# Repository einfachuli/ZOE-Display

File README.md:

# ZOE-Display

<pre>
!!!!!!!!!!!!!!!!!!!!!!!!!!!!!!!!!!!!!!!!!!!!!!!!!!!!!!!!!!!!!!!!!!
!!!! OHNE GEWÄHR, ALLES AUF EIGENE GEFAHR, NUR ZU TESTZWECKEN !!!!
!!!!!!!!!!!!!!!!!!!!!!!!!!!!!!!!!!!!!!!!!!!!!!!!!!!!!!!!!!!!!!!!!!
</pre>

## Verwendete Bauteile

- ESP32-Development-Board (z.B. https://www.ebay.de/itm/162572643462 oder https://www.amazon.de/gp/product/B071P98VTG)
- 2,8 Zoll 240 x 320 SPI TFT Panel resistiver Touchscreen (mit Display-Treiber ILI9341, z.B. https://www.amazon.de/gp/product/B0749N3S33/)
- alternativ mit kapazitivem Touchscreen (Adafruit 1947 mit Display-Treiber ILI9341, z.B. https://www.amazon.de/gp/product/B00R3R65C0/ oder https://www.mouser.de/ProductDetail/Adafruit/1947?qs=GURawfaeGuArmJSJoJoDJA%3D%3D)
- SD-Karte (bei resistivem Touchscreen) bzw. microSD-Karte (bei kapazitivem Touchscreen)
- optional GPS-Modul (z.B. https://www.ebay.de/itm/163636495985 oder https://www.amazon.de/gp/product/B01N38EMBF/)
- Kleinteile (siehe Ordner zur jeweiligen Platinen-Version)

## Verbindungen mit resistivem Touchscreen
<pre>
ESP32 Dev Board Pinout

Wohin           Bezeich.       ESP32 Pins       Bezeich.    Wohin

                            3V3         GND
                            EN          G23     MOSI        Display,Touch,SD
                ST          G36         G22
                            G39         G1      (TX)
                            G34         G3      (RX)
                (CAN2 RX)   G35         G21     CS          Touch
                (CAN2 TX)   G32         GND
                HR          G33         G19     MISO        Display,Touch,SD
                            G25         G18     SCLK        Display,Touch,SD
GPS             GPS TX      G26         G5 
GPS             GPS RX      G27         G17     CAN TX      CAN Bus
BUZZER+                     G14         G16     CAN RX      CAN Bus 
                POWER OFF   G12         G4      RST         Display
                            GND         G0      (BOOT)
SD              CS          G13         G2      DC          Display
                (Flash)     G9          G15     CS          Display
                (Flash)     G10         G8      (Flash)
                (Flash)     G11         G7      (Flash)
                            5V          G6      (Flash)
</pre>                    
RX und TX gibt den Pin an, mit dem es verbunden werden muss. GPS TX muss also auf den Pin
TX am GPS Modul! 

CAN2 ist derzeit experimentell. 

ST = Screen Turn, ST=1 (mit 10k auf 3V3) -> Bildschirm um 180 Grad gedreht

HR = Helligkeitsregelung, kann einen Transistor ansteuern, über den die LED-Hintergrundbeleuchtung des Displays gedimmt werden kann.

POWER OFF = Ausschalt-Pin für die Stromversorgung über den OBD-Port

## Verbindungen mit kapazitivem Touchscreen
<pre>
ESP32 Dev Board Pinout

Wohin           Bezeich.       ESP32 Pins       Bezeich.    Wohin

                            3V3         GND
                            EN          G23     SPI MOSI    Display
                ST          G36         G22     I²C SCL     Display
                            G39         G1      (TX)
                            G34         G3      (RX)
                (CAN2 RX)   G35         G21 
                (CAN2 TX)   G32         GND
Display         HR          G33         G19     SPI MISO    Display
Display         I²C SDA     G25         G18     SPI SCLK    Display
GPS             GPS TX      G26         G5
GPS             GPS RX      G27         G17     CAN TX      CAN Bus
BUZZER+                     G14         G16     CAN RX      CAN Bus 
                POWER OFF   G12         G4      RST         Display
                            GND         G0      (BOOT)
Display         CARDCS      G13         G2      DC          Display
                (Flash)     G9          G15     CS          Display
                (Flash)     G10         G8      (Flash)
                (Flash)     G11         G7      (Flash)
                            5V          G6      (Flash)
</pre>                    
RX und TX gibt den Pin an, mit dem es verbunden werden muss. GPS TX muss also auf den Pin
TX am GPS Modul! 

CAN2 ist derzeit experimentell. 

ST = Screen Turn, ST=1 (mit 10k auf 3V3) -> Bildschirm um 180 Grad gedreht

HR = Helligkeitsregelung, an Pin GPIO33 liegt ein PWM Signal an, welches über Pin D5 am Display
(neben CARDCS) die Regelung der Displayhelligkeit erlaubt. Achtung: Die Lötbrücke #5 auf der 
Displayplatine muss hierfür gesetzt werden.

POWER OFF = Ausschalt-Pin für die Stromversorgung über den OBD-Port
                    
## Allgemein
-  Beim Betrieb des resistiven Displays mit 3,3 V sollte der Jumper J1 am Display gesetzt (verbunden) werden (Ausschalten
des Spannungsreglers des Displays, sonst sinken die 3,3 V auf irgendwas unter 3 V). Der Touch IRQ Pin bleibt leer.
- Das Display mit kapazitivem Touchscreen erhält 5 V Versorgungsspannung. Falls das verwendete Display keine IOREF-Lötbrücke besitzt bzw. diese auf 5 V gesetzt wurde, muss eine geeignete Maßnahme vorgesehen werden, um die Spannungspegel am I²C-Bus auf max. 3,3 V zu begrenzen (das Display zieht die Leitungen nämlich mit 10-kΩ-Pull-Up-Widerständen gegen 5 V).

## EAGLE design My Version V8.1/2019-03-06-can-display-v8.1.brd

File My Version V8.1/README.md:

# Platine und kap. Einleger V8.1

von einfachuli (ZOE-Aachen)

<pre>

!!!!!!!!!!!!!!!!!!!!!!!!!!!!!!!!!!!!!!!!!!!!!!!!!!!!!!!!!!!!!!!!!!
!!!! OHNE GEWÄHR, ALLES AUF EIGENE GEFAHR, NUR ZU TESTZWECKEN !!!!
!!!! Das Projekt ist für Messe- und Laborzwecke bestimmt      !!!!
!!!!!und für die Verwendung im Bereich der StVO nicht zugelassen!!
!!!!!!!!!!!!!!!!!!!!!!!!!!!!!!!!!!!!!!!!!!!!!!!!!!!!!!!!!!!!!!!!!!

</pre>

##  Versionshinweise V8.1

- kap. Display nur mit ioref 3V unterstützt ! keine PullDowns R4 und R7 am I2C Bus, da ich nur Displays mit ioref verwende 

- statt Lötbrücke SJ2 für die 5V Stromversorgung kap. Display über ESP USB Anschluss, Kodierbrücke bei Bedarf auf Jumper steckbar

- ich verwende Sockelleisten um den ESP und ggf auch das GPS zu sockeln. Sockelleisten sind dabei nur 5,7 mm hoch.

- kapazitive Display wird direkt auf die Pinabstandsleiste des Displays gelötet und sitzt damit 1,6 mm tiefer im Einleger. 
   --> Dazu mussen die Lötstellen auf der Platine sauber geschnitten werden.

- ggf. Reset- bzw. Ein-Aus-Schalter, als Unterbrecher vor der 12V+ Klemme.

- resistives Display und Spannungsregler U2 Version OKI-78SR-5/1.5-W36-C ist von der Höhe ungünstig, wenn es in die Mulde passen soll.      Besser ist hier eine niedrigere Bauform, wie z.B. bei Gaptec LMP78_05-1.5 DC/DC-Wandler

## Bilddoku: 
  siehe https://github.com/einfachuli/ZOE-Display/tree/master/My%20Version%20V8.1/Bilder

## alles Weitere steht in der Bauanleitung Version Platine V8. 
  siehe https://github.com/einfachuli/ZOE-Display/blob/master/Platine%20V8/README.md

## Bezugsquellen zusätzlich verwendete Bauteile:

  - Codierbrücke: https://www.conrad.de/de/p/codierbruecke-cab-pole-2-cab-9-g-r-fischer-elektronik-736318.html

  - niedrige Sockelleisten: https://www.reichelt.de/buchsenleiste-36-polig-vergoldet-2-54-bkl-10120802-p235673.html?

  - U2 Version flach: https://www.conrad.de/de/p/gaptec-lmp78-05-1-5-dc-dc-wandler-print-24-v-dc-5-v-dc-1500-ma-7-5-w-anzahl-ausgaenge-1-x-1603649.html

  - Reset Drucktaster: https://www.conrad.de/de/p/sci-r13-502b-05rt-drucktaster-250-v-ac-1-5-a-1-x-ein-aus-tastend-1-st-701100.html

  - 3D Drucke: https://www.s3dproducts.de/

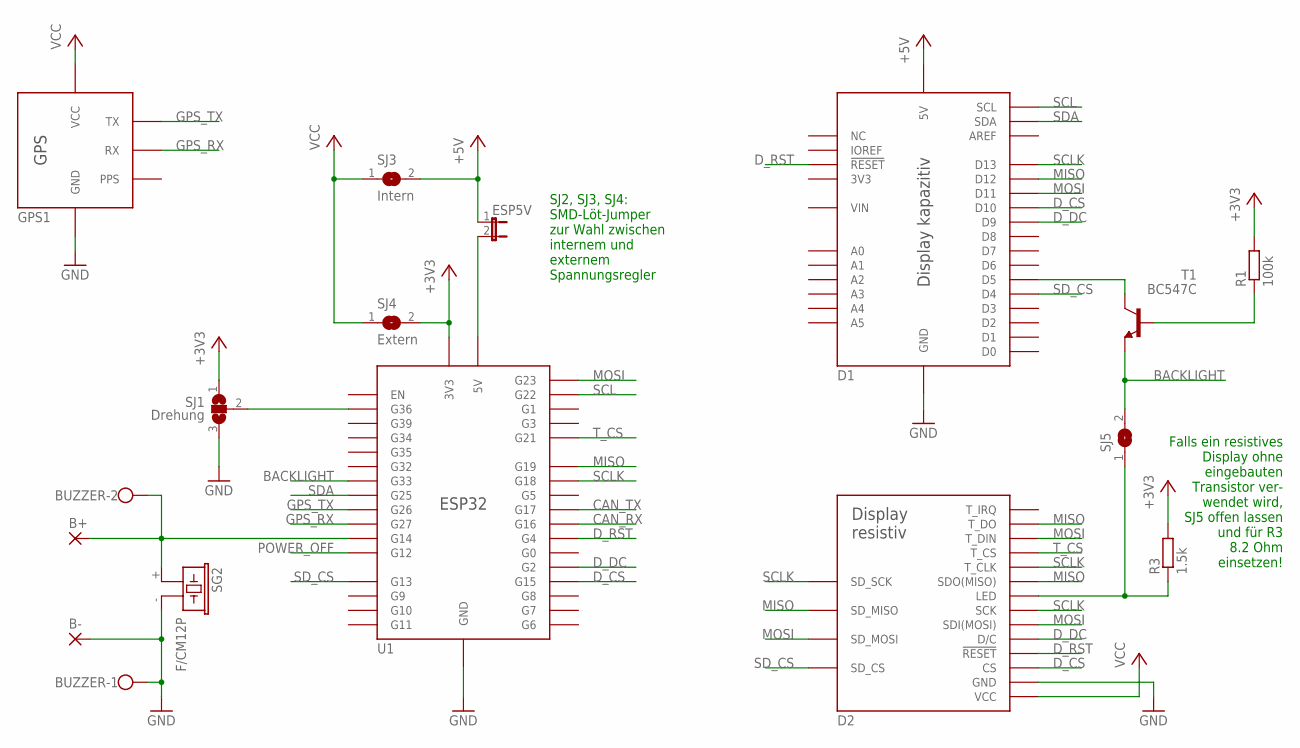
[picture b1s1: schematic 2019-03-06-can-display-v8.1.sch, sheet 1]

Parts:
B+: WIREPADSMD5-2,5; 5-2,5
B-: WIREPADSMD5-2,5; 5-2,5
BUZZER: W237-102
D1: TFT-KAPAZITIV
D2: TFT-RESISTIV
ESP5V: ESP 5V; JP1
GPS1: GPS
R1: 100k; VMTA55
R3: 1.5k; VMTA55
SG2: F/CM12P
SJ1: Drehung; SJ_2
SJ3: Intern; SJ
SJ4: Extern; SJ
SJ5: const.; SJ
T1: BC547C; TO92
U1: ESP32

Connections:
+3V3: R1.2, R3.2, SJ1.1, SJ4.2, U1.3V3, U1.3V3S (3V3); also elsewhere on the board
+5V: D1.5V, ESP5V.1, SJ3.2; also elsewhere on the board
BACKLIGHT: SJ5.2, T1.1 (E), U1.G33, U1.G33S (G33)
BUZZER: B+.1, BUZZER.2, SG2.+ (1), U1.G14, U1.G14S (G14)
CAN_RX: U1.G16; also elsewhere on the board
CAN_TX: U1.G17; also elsewhere on the board
DIS-BL: D2.LED, R3.1, SJ5.1
D_CS: D1.D10, D2.LCD_CS (CS), U1.G15
D_DC: D1.D9, D2.LCD_DC (D/C), U1.G2
D_RST: D1.RESET (!RESET!), D2.LCD_RESET (!RESET!), U1.G4
ESP5V: ESP5V.2, U1.5V, U1.5VS (5V)
GND: B-.1, BUZZER.1, D1.GND@1 (GND), D1.GND@2 (GND), D1.GND@3 (GND), D2.GND, GPS1.GND1 (GND), GPS1.GND2 (GND), SG2.- (2), SJ1.3, U1.GND@1 (GND), U1.GND@2 (GND), U1.GND@3 (GND), U1.GND@4 (GND); also elsewhere on the board
GPS_RX: GPS1.RX1 (RX), GPS1.RX2 (RX), U1.G27, U1.G27S (G27)
GPS_TX: GPS1.TX1 (TX), GPS1.TX2 (TX), U1.G26, U1.G26S (G26)
MISO: D1.D12, D2.LCD_MISO (SDO(MISO)), D2.SD_MISO, D2.T_DO, U1.G19
MOSI: D1.D11, D2.LCD_MOSI (SDI(MOSI)), D2.SD_MOSI, D2.T_DIN, U1.G23
unnamed: SJ1.2, U1.G36, U1.G36S (G36)
unnamed: D1.D5, T1.3 (C)
unnamed: R1.1, T1.2 (B)
POWER_OFF: U1.G12, U1.G12S (G12); also elsewhere on the board
SCL: D1.KAP_SCL (SCL), U1.G22
SCLK: D1.D13, D2.LCD_SCK (SCK), D2.SD_SCK, D2.T_CLK, U1.G18
SDA: D1.KAP_SDA (SDA), U1.G25, U1.G25S (G25)
SD_CS: D1.D4, D2.SD_CS, U1.G13, U1.G13S (G13)
T_CS: D2.T_CS, U1.G21
VCC: D2.VCC, GPS1.VCC1 (VCC), GPS1.VCC2 (VCC), SJ3.1, SJ4.1; also elsewhere on the board

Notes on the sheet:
SJ2, SJ3, SJ4: SMD-Löt-Jumper zur Wahl zwischen internem und externem Spannungsregler
Falls ein resistives Display ohne eingebauten Transistor ver- wendet wird, SJ5 offen lassen und für R3 8.2 Ohm einsetzen!

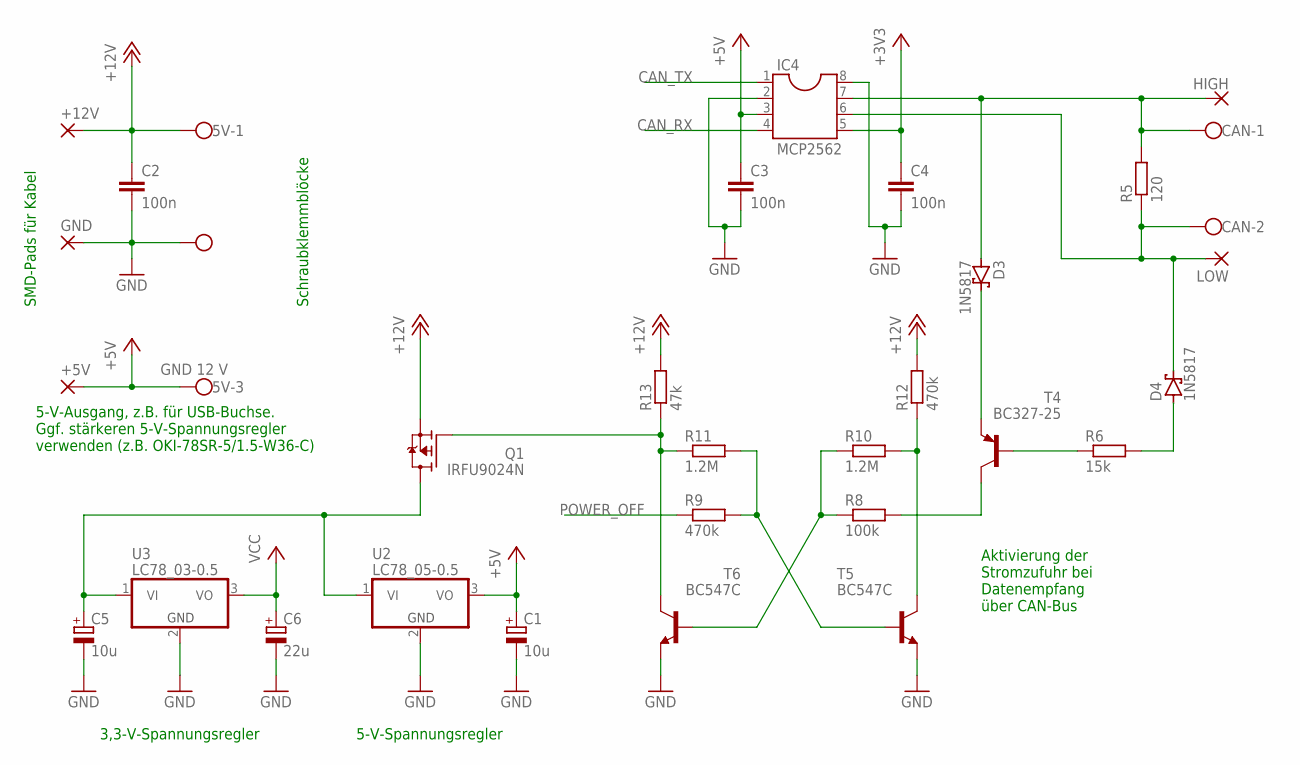
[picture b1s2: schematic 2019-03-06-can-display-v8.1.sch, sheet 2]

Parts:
5V: GND 12 V; W237-103
+5V, +12V: WIREPADSMD5-2,5; 5-2,5
C1, C5: 10u; E1,8-4
C2, C3, C4: 100n; C025-025X050
C6: 22u; E1,8-4
CAN: W237-102
D3, D4: 1N5817; DO41-7.6
GND: WIREPADSMD5-2,5; 5-2,5
HIGH: WIREPADSMD5-2,5; 5-2,5
IC4: MCP2562; DIL08
LOW: WIREPADSMD5-2,5; 5-2,5
Q1: IRFU9024N; TO251AA-V
R5: 120; VMTA55
R6: 15k; VMTA55
R8: 100k; VMTA55
R9, R12: 470k; VMTA55
R10, R11: 1.2M; VMTA55
R13: 47k; VMTA55
T4: BC327-25; TO92
T5, T6: BC547C; TO92
U2: LC78_05-0.5; SPANNUNGSREGLER
U3: LC78_03-0.5; SPANNUNGSREGLER

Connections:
+3V3: C4.1, IC4.5; also elsewhere on the board
+5V: 5V.3, +5V.1, C1.+, C3.1, IC4.3, U2.3 (VO); also elsewhere on the board
+12V: 5V.1, +12V.1, C2.1, Q1.3 (S), R12.2, R13.2
CAN_RX: IC4.4; also elsewhere on the board
CAN_TX: IC4.1; also elsewhere on the board
GND: 5V.2, C1.-, C2.2, C3.2, C4.2, C5.-, C6.-, GND.1, IC4.2, IC4.8, T5.1 (E), T6.1 (E), U2.2 (GND), U3.2 (GND); also elsewhere on the board
unnamed: D3.C, T4.1 (E)
unnamed: R6.1, T4.2 (B)
unnamed: D4.A, R6.2
unnamed: R8.1, R10.1, T6.2 (B)
unnamed: CAN.1, D3.A, HIGH.1, IC4.7, R5.2
unnamed: CAN.2, D4.C, IC4.6, LOW.1, R5.1
unnamed: R8.2, T4.3 (C)
unnamed: R9.2, R11.2, T5.2 (B)
unnamed: R10.2, R12.1, T5.3 (C)
unnamed: Q1.1 (G), R11.1, R13.1, T6.3 (C)
unnamed: C5.+, Q1.2 (D), U2.1 (VI), U3.1 (VI)
POWER_OFF: R9.1; also elsewhere on the board
VCC: C6.+, U3.3 (VO); also elsewhere on the board

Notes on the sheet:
3,3-V-Spannungsregler
5-V-Spannungsregler
Aktivierung der Stromzufuhr bei Datenempfang über CAN-Bus
SMD-Pads für Kabel
Schraubklemmblöcke
5-V-Ausgang, z.B. für USB-Buchse. Ggf. stärkeren 5-V-Spannungsregler verwenden (z.B. OKI-78SR-5/1.5-W36-C)

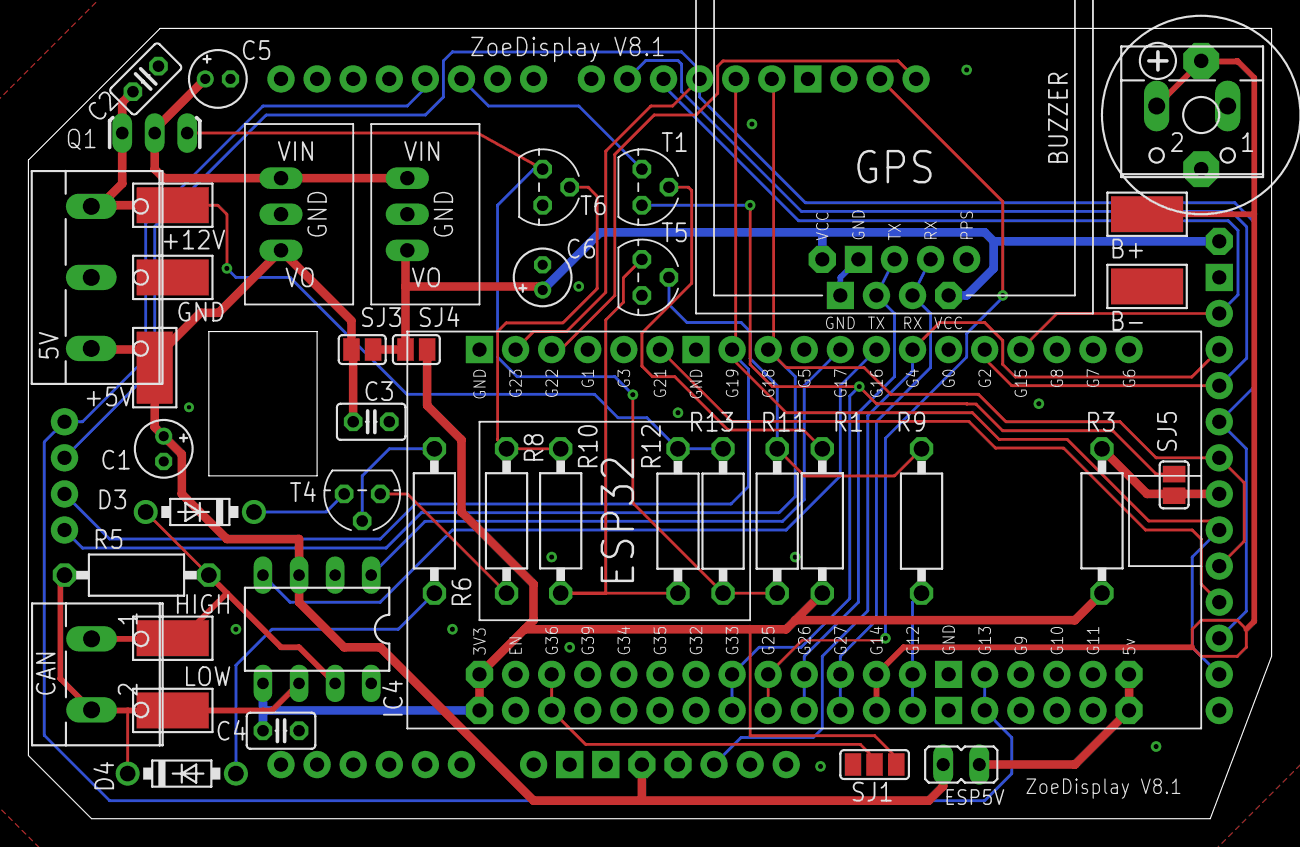
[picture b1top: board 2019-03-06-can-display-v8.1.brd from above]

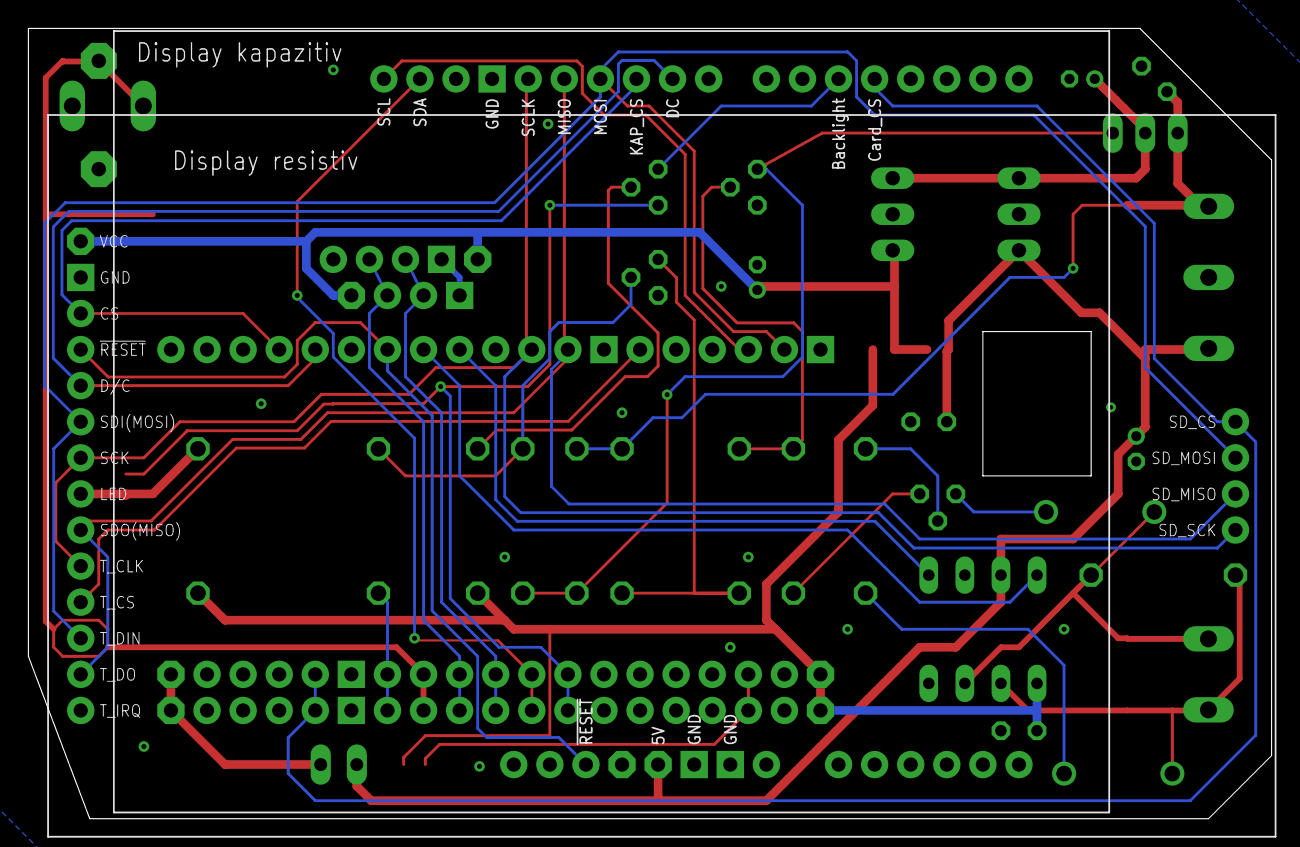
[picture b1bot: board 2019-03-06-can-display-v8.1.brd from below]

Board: 2 copper layers, 87.5 x 55.6 mm, 46 parts (2 on the bottom side), 38 nets.

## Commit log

2019-06-30 Eagle Files meiner Platinenversion
    Jumper für SJ2 5V von ESP eingefügt. Kann jetzt bei Bedarf gesetzt werden.
    C2 versetzt. Transitoren neu ausgerichtet. R4 und R7 entfernt, alle Displays hatten ioref. kleine Änderungen der Traces.
2019-06-30 Kapazitiven Einleger angepasst
    Platinenauflage um 1,6 mm tiefergelegt. Damit kann die Planine näher an das Display gesetzt werden. Alles wird etwas weniger hoch.
2019-06-30 meine Version 8.1 black Edition mit Reset
    ESP ist gesockelt, Reset unterbricht die 12V+, Einleger ist in PETG mit Carbonanteil gedruckt.
2019-06-30 meine Version 8.1 grau mit Reset
    ESP ist gesockelt, Reset unterbricht die 12V+, Einleger ist in PETG gedruckt.
2019-06-30 resistves Display gesockelt, zerlegbar
    ESP, GPS und Platine-Display Verbingung sind gesockelt.
2019-06-30 screenshots
2019-06-30 SPI Flash speed angepasst
    40MHz->80MHz
2019-06-30 Hinweis Framwork Version
2019-06-30 Lizenzfile von der Display Software kopiert
2019-06-30 Versionshinweise V8.1
2019-07-10 Delete CAN-ESP32.ZOE.esp32-v2.072.bin
    old Software deleted
2019-07-10 Create CAN-ESP32.ZOE.esp32-v2.087.bin
    Software with ESP Framework 1.0.1
2019-07-10 Create CAN-ESP32.ZOE.esp32-v2.112.bin
    Software with ESP Framwork 1.0.2
2019-07-10 Create changelog.txt
    Download of Changelog V2.112
2019-07-10 Übersicht - Gallerie
2019-07-17 Update README.md
    Anleitung Punkt 2. angepasst
